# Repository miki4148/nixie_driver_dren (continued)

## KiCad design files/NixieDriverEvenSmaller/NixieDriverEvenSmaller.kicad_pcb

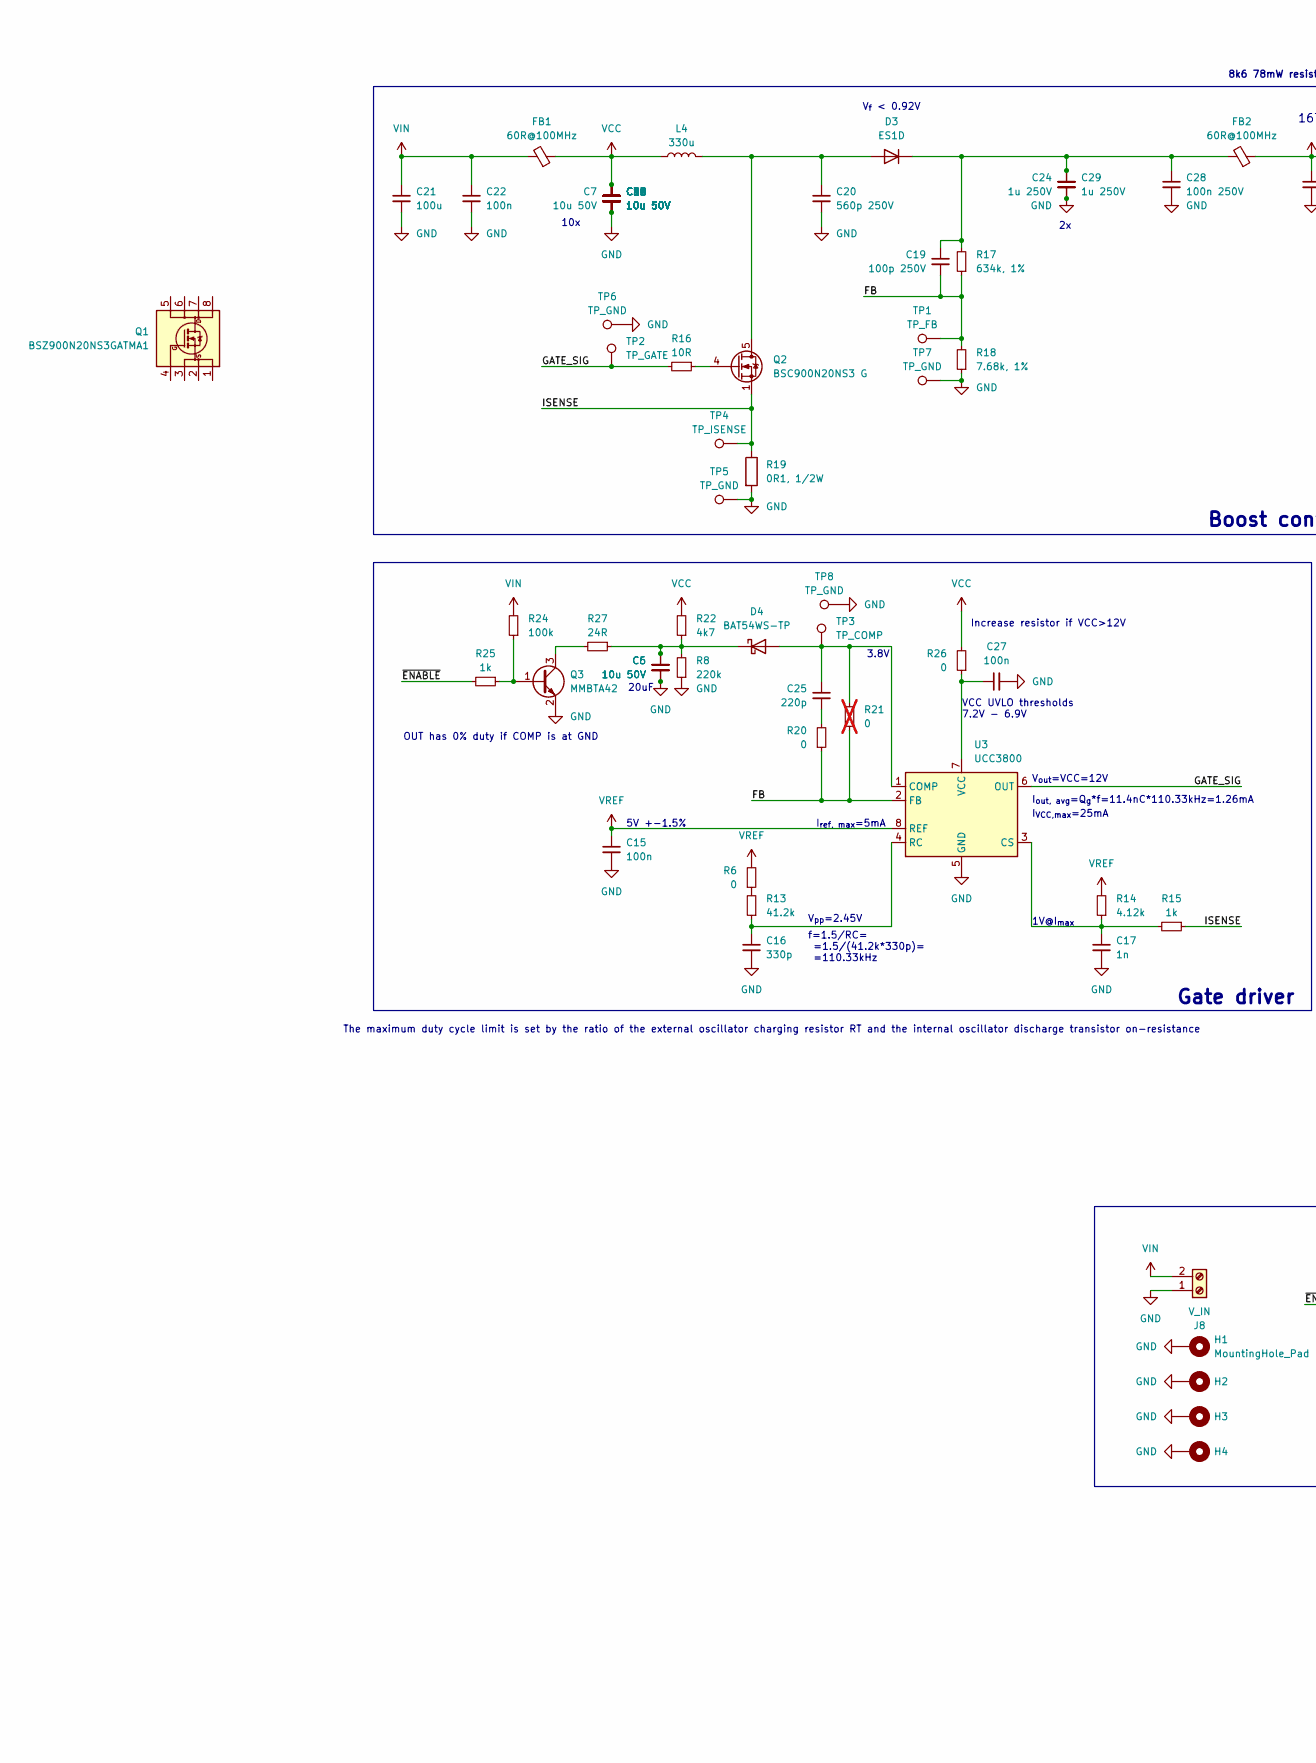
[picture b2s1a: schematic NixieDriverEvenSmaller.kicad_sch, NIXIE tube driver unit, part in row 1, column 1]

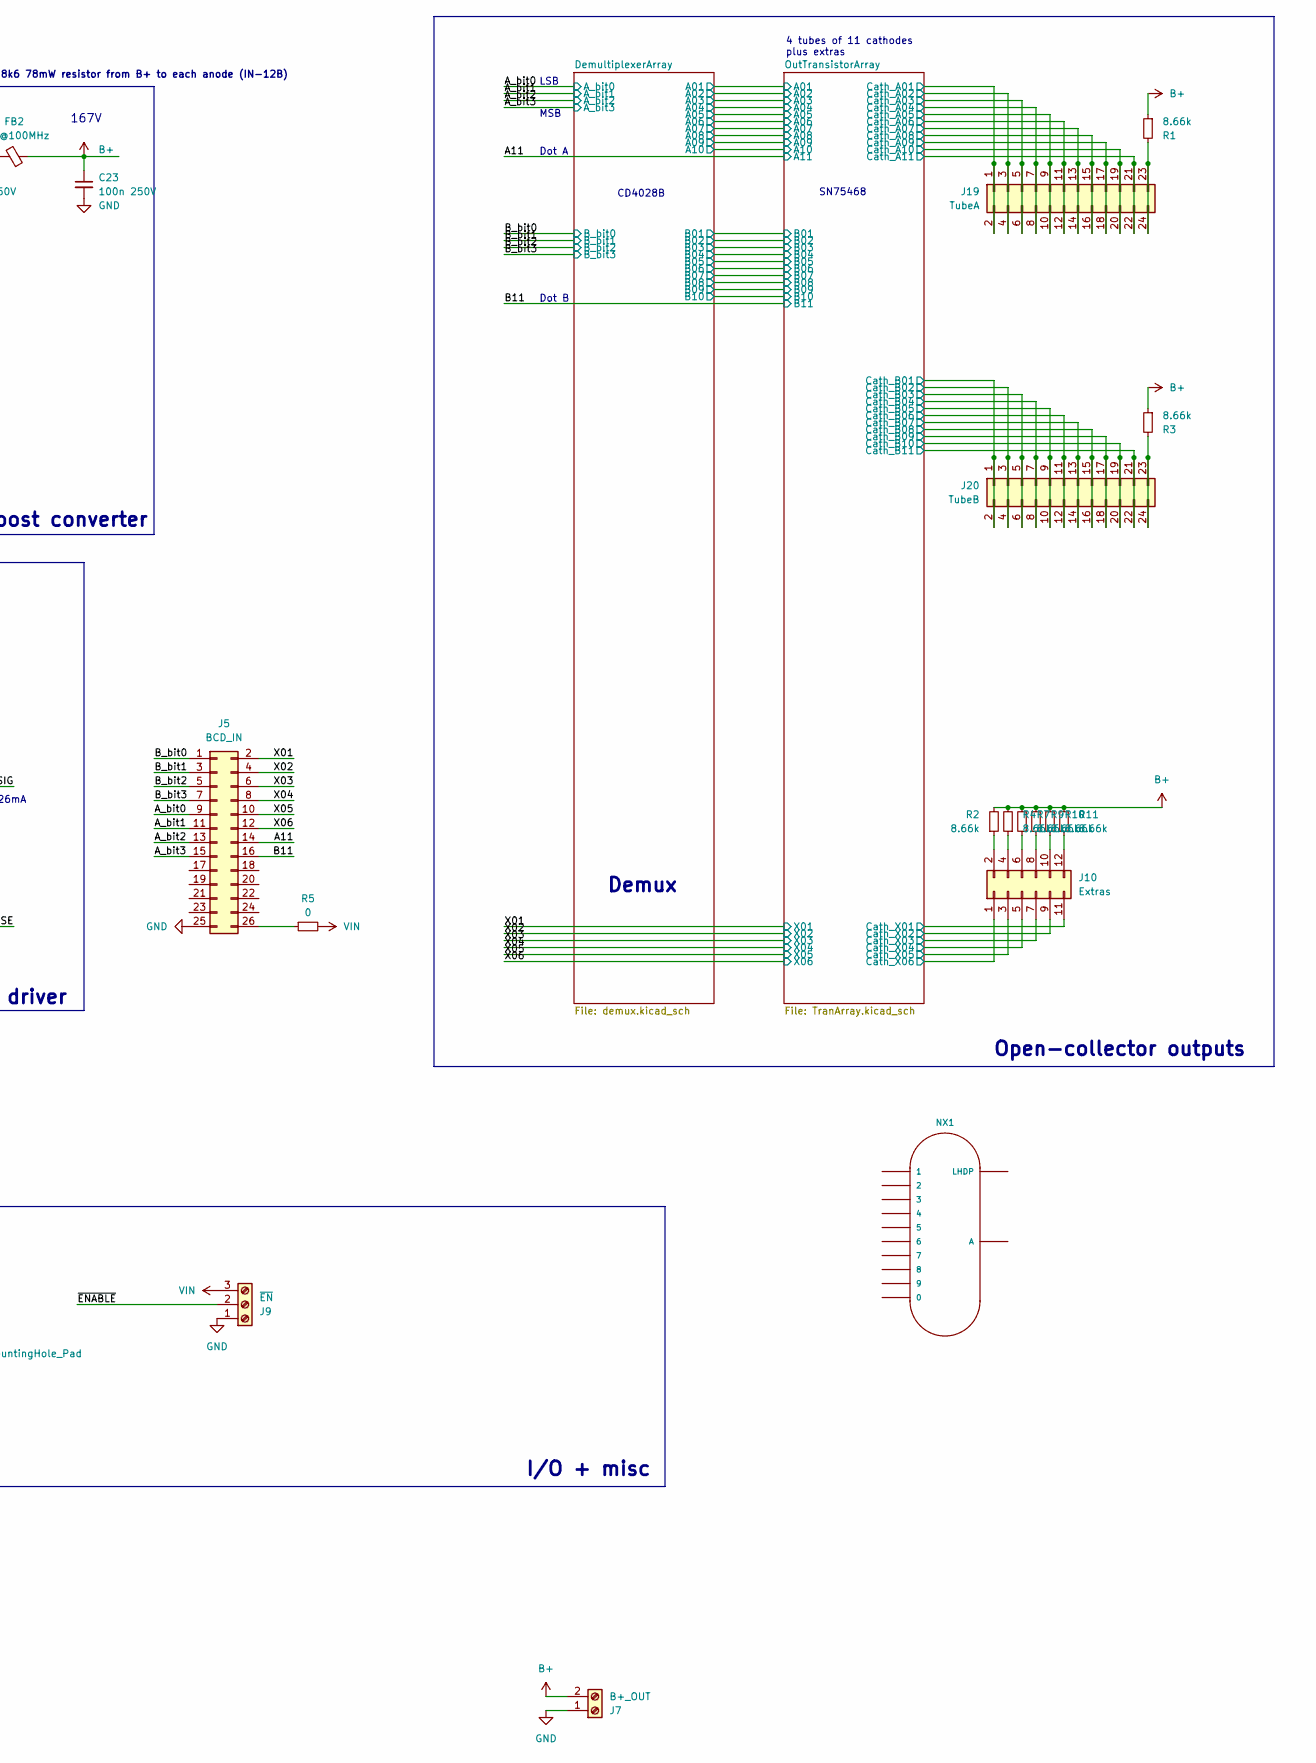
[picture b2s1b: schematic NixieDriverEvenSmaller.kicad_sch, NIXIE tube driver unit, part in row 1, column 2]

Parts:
C5, C6, C7, C8, C9, C10, C11, C12, C13, C14, C18, C30: 10u 50V; C_1206_3216Metric
C15, C22, C27: 100n; C_0603_1608Metric
C16: 330p; C_0603_1608Metric
C17: 1n; C_0603_1608Metric
C19: 100p 250V; C_1206_3216Metric
C20: 560p 250V; C_1206_3216Metric
C21: 100u; C_0603_1608Metric
C23, C28: 100n 250V; C_1206_3216Metric
C24, C29: 1u 250V; C_2220_5750Metric
C25: 220p; C_0603_1608Metric
D3: ES1D; D_SMA
D4: BAT54WS-TP; D_SOD-323_HandSoldering; MPN BAT54WS-7-F
FB1, FB2: 60R@100MHz; L_0603_1608Metric
H1, H2, H3, H4: MountingHole_Pad; MountingHole_3.2mm_M3_Pad
J5: BCD_IN; PinHeader_2x13_P1.27mm_Vertical_SMD
J7: B+_OUT; PinHeader_1x02_P2.00mm_Vertical
J8: V_IN; PinHeader_1x02_P2.00mm_Vertical
J9: ~{EN}; PinHeader_1x03_P2.00mm_Vertical
J10: Extras; PinSocket_2x06_P2.54mm_Vertical
J19: TubeA; PinSocket_2x12_P2.54mm_Vertical
J20: TubeB; PinSocket_2x12_P2.54mm_Vertical
L4: 330u; L_12x12mm_H8mm
NX1: IN-12BORIGINAL; nixies-us_IN-12
Q1: BSZ900N20NS3GATMA1; MPN FDS2672CT-ND
Q2: BSC900N20NS3 G; Infineon_PG-TDSON-8_6.15x5.15mm
Q3: MMBTA42; SOT-23
R1, R2, R3, R4, R7, R9, R10, R11: 8.66k; R_0805_2012Metric_Pad1.20x1.40mm_HandSolder
R5, R6, R20, R26: 0; R_0603_1608Metric
R8: 220k; R_0603_1608Metric
R13: 41.2k; R_0603_1608Metric
R14: 4.12k; R_0603_1608Metric
R15, R25: 1k; R_0603_1608Metric
R16: 10R; R_0603_1608Metric
R17: 634k, 1%; R_1206_3216Metric
R18: 7.68k, 1%; R_1206_3216Metric
R19: 0R1, 1/2W; R_1206_3216Metric
R21: 0; R_0603_1608Metric; not fitted
R22: 4k7; R_0603_1608Metric
R24: 100k; R_0603_1608Metric
R27: 24R; R_0603_1608Metric
TP1: TP_FB; TestPoint_Pad_D1.0mm
TP2: TP_GATE; TestPoint_Pad_D1.0mm
TP3: TP_COMP; TestPoint_Pad_D1.0mm
TP4: TP_ISENSE; TestPoint_Pad_D1.0mm
TP5, TP6, TP7, TP8: TP_GND; TestPoint_Pad_1.0x1.0mm
U3: UCC3800; SOIC-8_3.9x4.9mm_P1.27mm

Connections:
/A11: J5.14; also elsewhere on the board
/A_bit0: J5.9; also elsewhere on the board
/A_bit1: J5.11; also elsewhere on the board
/A_bit2: J5.13; also elsewhere on the board
/A_bit3: J5.15; also elsewhere on the board
/B11: J5.16; also elsewhere on the board
/B_bit0: J5.1; also elsewhere on the board
/B_bit1: J5.3; also elsewhere on the board
/B_bit2: J5.5; also elsewhere on the board
/B_bit3: J5.7; also elsewhere on the board
/FB: C19.2, R17.1, R18.2, R20.1, R21.1, TP1.1, U3.2 (FB)
/GATE_SIG: R16.2, TP2.1, U3.6 (OUT)
/ISENSE: Q2.1 (S), Q2.2 (S), Q2.3 (S), R15.1, R19.1, TP4.1
/OutTransistorArray/Cath_A01: J19.1, J19.2; also elsewhere on the board
/OutTransistorArray/Cath_A02: J19.3, J19.4; also elsewhere on the board
/OutTransistorArray/Cath_A03: J19.5, J19.6; also elsewhere on the board
/OutTransistorArray/Cath_A04: J19.7, J19.8; also elsewhere on the board
/OutTransistorArray/Cath_A05: J19.9, J19.10; also elsewhere on the board
/OutTransistorArray/Cath_A06: J19.11, J19.12; also elsewhere on the board
/OutTransistorArray/Cath_A07: J19.13, J19.14; also elsewhere on the board
/OutTransistorArray/Cath_A08: J19.15, J19.16; also elsewhere on the board
/OutTransistorArray/Cath_A09: J19.17, J19.18; also elsewhere on the board
/OutTransistorArray/Cath_A10: J19.19, J19.20; also elsewhere on the board
/OutTransistorArray/Cath_A11: J19.21, J19.22; also elsewhere on the board
/OutTransistorArray/Cath_B01: J20.1, J20.2; also elsewhere on the board
/OutTransistorArray/Cath_B02: J20.3, J20.4; also elsewhere on the board
/OutTransistorArray/Cath_B03: J20.5, J20.6; also elsewhere on the board
/OutTransistorArray/Cath_B04: J20.7, J20.8; also elsewhere on the board
/OutTransistorArray/Cath_B05: J20.9, J20.10; also elsewhere on the board
/OutTransistorArray/Cath_B06: J20.11, J20.12; also elsewhere on the board
/OutTransistorArray/Cath_B07: J20.13, J20.14; also elsewhere on the board
/OutTransistorArray/Cath_B08: J20.15, J20.16; also elsewhere on the board
/OutTransistorArray/Cath_B09: J20.17, J20.18; also elsewhere on the board
/OutTransistorArray/Cath_B10: J20.19, J20.20; also elsewhere on the board
/OutTransistorArray/Cath_B11: J20.21, J20.22; also elsewhere on the board
/OutTransistorArray/Cath_X01: J10.11; also elsewhere on the board
/OutTransistorArray/Cath_X02: J10.9; also elsewhere on the board
/OutTransistorArray/Cath_X03: J10.7; also elsewhere on the board
/OutTransistorArray/Cath_X04: J10.5; also elsewhere on the board
/OutTransistorArray/Cath_X05: J10.3; also elsewhere on the board
/OutTransistorArray/Cath_X06: J10.1; also elsewhere on the board
/X01: J5.2; also elsewhere on the board
/X02: J5.4; also elsewhere on the board
/X03: J5.6; also elsewhere on the board
/X04: J5.8; also elsewhere on the board
/X05: J5.10; also elsewhere on the board
/X06: J5.12; also elsewhere on the board
/~ENABLE: J9.2, R25.2
B+: C23.1, FB2.1, J7.2, R1.1, R2.2, R3.1, R4.2, R7.2, R9.2, R10.2, R11.2
GND: C5.2, C6.2, C7.2, C8.2, C9.2, C10.2, C11.2, C12.2, C13.2, C14.2, C15.2, C16.2, C17.2, C18.2, C20.2, C21.2, C22.2, C23.2, C24.2, C27.2, C28.2, C29.2, C30.2, H1.1, H2.1, H3.1, H4.1, J5.25, J7.1, J8.1, J9.1, Q3.2 (E), R8.1, R18.1, R19.2, TP5.1, TP6.1, TP7.1, TP8.1, U3.5 (GND); also elsewhere on the board
unnamed: C25.2, R20.2
unnamed: C20.1, D3.2 (A), L4.2, Q2.5 (D)
unnamed: C19.1, C24.1, C28.1, C29.1, D3.1 (K), FB2.2, R17.2
unnamed: C25.1, D4.2 (A), R21.2, TP3.1, U3.1 (COMP)
unnamed: C5.1, C6.1, D4.1 (K), R8.2, R22.1, R27.1
unnamed: J5.26, R5.1
unnamed: J10.2, R2.1
unnamed: J10.4, R4.1
unnamed: J10.6, R7.1
unnamed: J10.8, R9.1
unnamed: J10.10, R10.1
unnamed: J10.12, R11.1
unnamed: J19.23, J19.24, R1.2
unnamed: J20.23, J20.24, R3.2
unnamed: Q2.4 (G), R16.1
unnamed: Q3.1 (B), R24.1, R25.1
unnamed: Q3.3 (C), R27.2
unnamed: R6.1, R13.2
unnamed: C17.1, R14.1, R15.2, U3.3 (CS)
unnamed: C16.1, R13.1, U3.4 (RC)
unnamed: C27.1, R26.1, U3.7 (VCC)
VCC: C7.1, C8.1, C9.1, C10.1, C11.1, C12.1, C13.1, C14.1, C18.1, C30.1, FB1.1, L4.1, R22.2, R26.2
VIN: C21.1, C22.1, FB1.2, J8.2, J9.3, R5.2, R24.2; also elsewhere on the board
VREF: C15.1, R6.2, R14.2, U3.8 (REF)

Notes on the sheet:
4 tubes of 11 cathodes plus extras
8k6 78mW resistor from B+ to each anode (IN-12B)
Dot A
I_{ref, max}=5mA
OUT has 0% duty if COMP is at GND
I_{VCC,max}=25mA
1V@I_{max}
10x
V_{out}=VCC=12V
MSB
20uF
167V
f=1.5/RC= =1.5/(41.2k*330p)= =110.33kHz
3.8V
I/O + misc
Demux
CD4028B
V_{f} < 0.92V
Gate driver
I_{out, avg}=Q_{g}*f=11.4nC*110.33kHz=1.26mA
VCC UVLO thresholds 7.2V - 6.9V
V_{pp}=2.45V
The maximum duty cycle limit is set by the ratio of the external oscillator charging resistor RT and the internal oscillator discharge transistor on-resistance
Increase resistor if VCC>12V
SN75468
5V +-1.5%
Boost converter
Dot B
LSB
Open-collector outputs

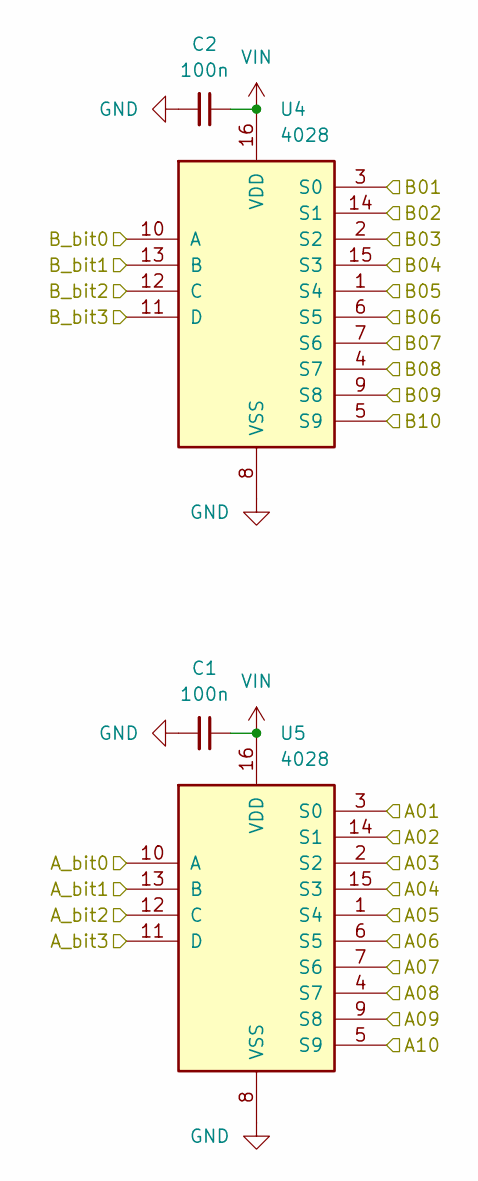
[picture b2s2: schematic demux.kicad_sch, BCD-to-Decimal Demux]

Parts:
C1, C2: 100n; C_0603_1608Metric
U4, U5: 4028; SOIC-16_3.9x9.9mm_P1.27mm

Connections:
/A_bit0: U5.10 (A); also elsewhere on the board
/A_bit1: U5.13 (B); also elsewhere on the board
/A_bit2: U5.12 (C); also elsewhere on the board
/A_bit3: U5.11 (D); also elsewhere on the board
/B_bit0: U4.10 (A); also elsewhere on the board
/B_bit1: U4.13 (B); also elsewhere on the board
/B_bit2: U4.12 (C); also elsewhere on the board
/B_bit3: U4.11 (D); also elsewhere on the board
/DemultiplexerArray/A01: U5.3 (S0); also elsewhere on the board
/DemultiplexerArray/A02: U5.14 (S1); also elsewhere on the board
/DemultiplexerArray/A03: U5.2 (S2); also elsewhere on the board
/DemultiplexerArray/A04: U5.15 (S3); also elsewhere on the board
/DemultiplexerArray/A05: U5.1 (S4); also elsewhere on the board
/DemultiplexerArray/A06: U5.6 (S5); also elsewhere on the board
/DemultiplexerArray/A07: U5.7 (S6); also elsewhere on the board
/DemultiplexerArray/A08: U5.4 (S7); also elsewhere on the board
/DemultiplexerArray/A09: U5.9 (S8); also elsewhere on the board
/DemultiplexerArray/A10: U5.5 (S9); also elsewhere on the board
/DemultiplexerArray/B01: U4.3 (S0); also elsewhere on the board
/DemultiplexerArray/B02: U4.14 (S1); also elsewhere on the board
/DemultiplexerArray/B03: U4.2 (S2); also elsewhere on the board
/DemultiplexerArray/B04: U4.15 (S3); also elsewhere on the board
/DemultiplexerArray/B05: U4.1 (S4); also elsewhere on the board
/DemultiplexerArray/B06: U4.6 (S5); also elsewhere on the board
/DemultiplexerArray/B07: U4.7 (S6); also elsewhere on the board
/DemultiplexerArray/B08: U4.4 (S7); also elsewhere on the board
/DemultiplexerArray/B09: U4.9 (S8); also elsewhere on the board
/DemultiplexerArray/B10: U4.5 (S9); also elsewhere on the board
GND: C1.2, C2.2, U4.8 (VSS), U5.8 (VSS); also elsewhere on the board
VIN: C1.1, C2.1, U4.16 (VDD), U5.16 (VDD); also elsewhere on the board

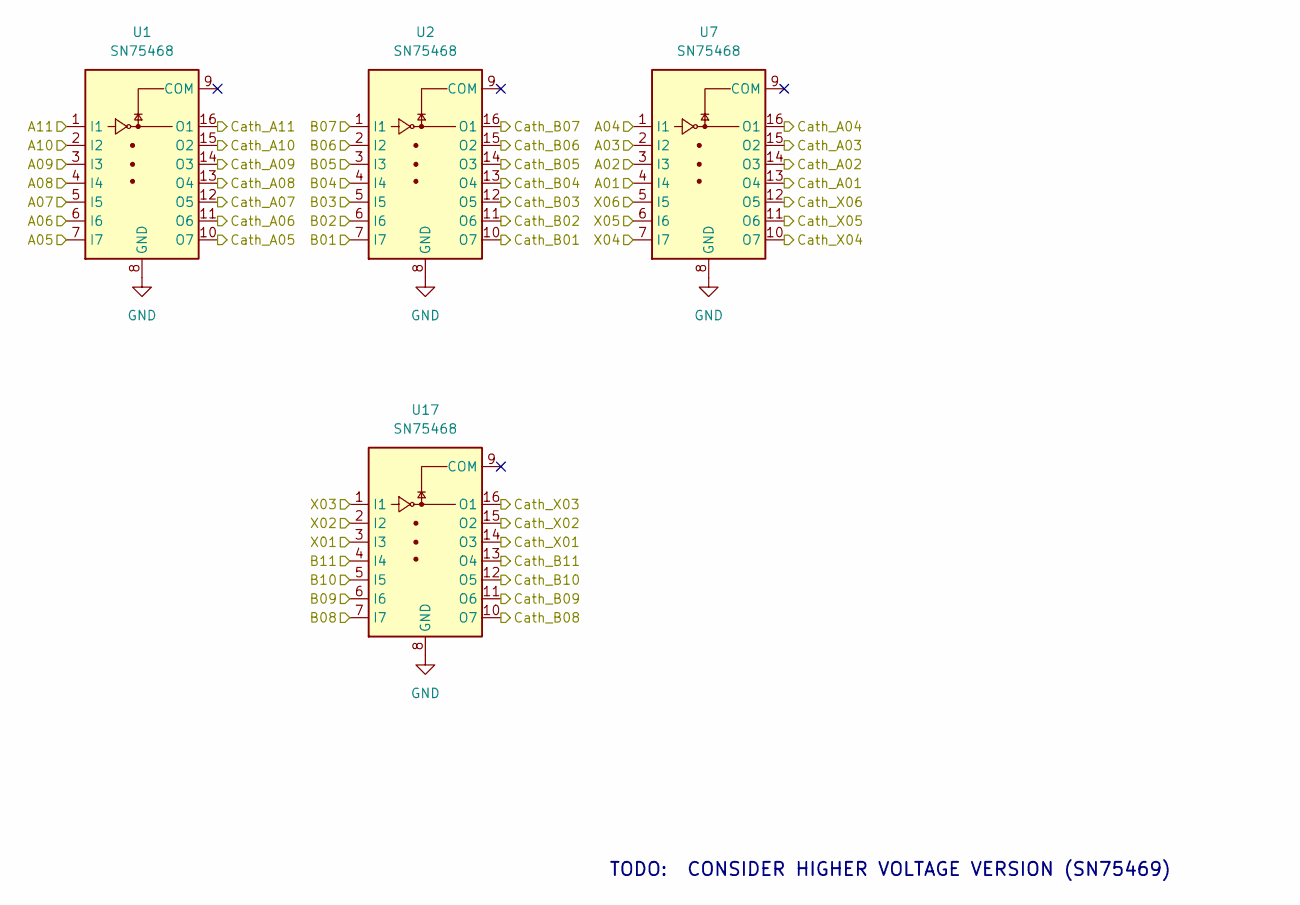
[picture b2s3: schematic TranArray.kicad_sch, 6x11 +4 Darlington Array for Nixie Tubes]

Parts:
U1, U2, U7, U17: SN75468; SOIC-16_3.9x9.9mm_P1.27mm

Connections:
/A11: U1.1 (I1); also elsewhere on the board
/B11: U17.4 (I4); also elsewhere on the board
/DemultiplexerArray/A01: U7.4 (I4); also elsewhere on the board
/DemultiplexerArray/A02: U7.3 (I3); also elsewhere on the board
/DemultiplexerArray/A03: U7.2 (I2); also elsewhere on the board
/DemultiplexerArray/A04: U7.1 (I1); also elsewhere on the board
/DemultiplexerArray/A05: U1.7 (I7); also elsewhere on the board
/DemultiplexerArray/A06: U1.6 (I6); also elsewhere on the board
/DemultiplexerArray/A07: U1.5 (I5); also elsewhere on the board
/DemultiplexerArray/A08: U1.4 (I4); also elsewhere on the board
/DemultiplexerArray/A09: U1.3 (I3); also elsewhere on the board
/DemultiplexerArray/A10: U1.2 (I2); also elsewhere on the board
/DemultiplexerArray/B01: U2.7 (I7); also elsewhere on the board
/DemultiplexerArray/B02: U2.6 (I6); also elsewhere on the board
/DemultiplexerArray/B03: U2.5 (I5); also elsewhere on the board
/DemultiplexerArray/B04: U2.4 (I4); also elsewhere on the board
/DemultiplexerArray/B05: U2.3 (I3); also elsewhere on the board
/DemultiplexerArray/B06: U2.2 (I2); also elsewhere on the board
/DemultiplexerArray/B07: U2.1 (I1); also elsewhere on the board
/DemultiplexerArray/B08: U17.7 (I7); also elsewhere on the board
/DemultiplexerArray/B09: U17.6 (I6); also elsewhere on the board
/DemultiplexerArray/B10: U17.5 (I5); also elsewhere on the board
/OutTransistorArray/Cath_A01: U7.13 (O4); also elsewhere on the board
/OutTransistorArray/Cath_A02: U7.14 (O3); also elsewhere on the board
/OutTransistorArray/Cath_A03: U7.15 (O2); also elsewhere on the board
/OutTransistorArray/Cath_A04: U7.16 (O1); also elsewhere on the board
/OutTransistorArray/Cath_A05: U1.10 (O7); also elsewhere on the board
/OutTransistorArray/Cath_A06: U1.11 (O6); also elsewhere on the board
/OutTransistorArray/Cath_A07: U1.12 (O5); also elsewhere on the board
/OutTransistorArray/Cath_A08: U1.13 (O4); also elsewhere on the board
/OutTransistorArray/Cath_A09: U1.14 (O3); also elsewhere on the board
/OutTransistorArray/Cath_A10: U1.15 (O2); also elsewhere on the board
/OutTransistorArray/Cath_A11: U1.16 (O1); also elsewhere on the board
/OutTransistorArray/Cath_B01: U2.10 (O7); also elsewhere on the board
/OutTransistorArray/Cath_B02: U2.11 (O6); also elsewhere on the board
/OutTransistorArray/Cath_B03: U2.12 (O5); also elsewhere on the board
/OutTransistorArray/Cath_B04: U2.13 (O4); also elsewhere on the board
/OutTransistorArray/Cath_B05: U2.14 (O3); also elsewhere on the board
/OutTransistorArray/Cath_B06: U2.15 (O2); also elsewhere on the board
/OutTransistorArray/Cath_B07: U2.16 (O1); also elsewhere on the board
/OutTransistorArray/Cath_B08: U17.10 (O7); also elsewhere on the board
/OutTransistorArray/Cath_B09: U17.11 (O6); also elsewhere on the board
/OutTransistorArray/Cath_B10: U17.12 (O5); also elsewhere on the board
/OutTransistorArray/Cath_B11: U17.13 (O4); also elsewhere on the board
/OutTransistorArray/Cath_X01: U17.14 (O3); also elsewhere on the board
/OutTransistorArray/Cath_X02: U17.15 (O2); also elsewhere on the board
/OutTransistorArray/Cath_X03: U17.16 (O1); also elsewhere on the board
/OutTransistorArray/Cath_X04: U7.10 (O7); also elsewhere on the board
/OutTransistorArray/Cath_X05: U7.11 (O6); also elsewhere on the board
/OutTransistorArray/Cath_X06: U7.12 (O5); also elsewhere on the board
/X01: U17.3 (I3); also elsewhere on the board
/X02: U17.2 (I2); also elsewhere on the board
/X03: U17.1 (I1); also elsewhere on the board
/X04: U7.7 (I7); also elsewhere on the board
/X05: U7.6 (I6); also elsewhere on the board
/X06: U7.5 (I5); also elsewhere on the board
GND: U1.8 (GND), U2.8 (GND), U7.8 (GND), U17.8 (GND); also elsewhere on the board

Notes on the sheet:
TODO: CONSIDER HIGHER VOLTAGE VERSION (SN75469)

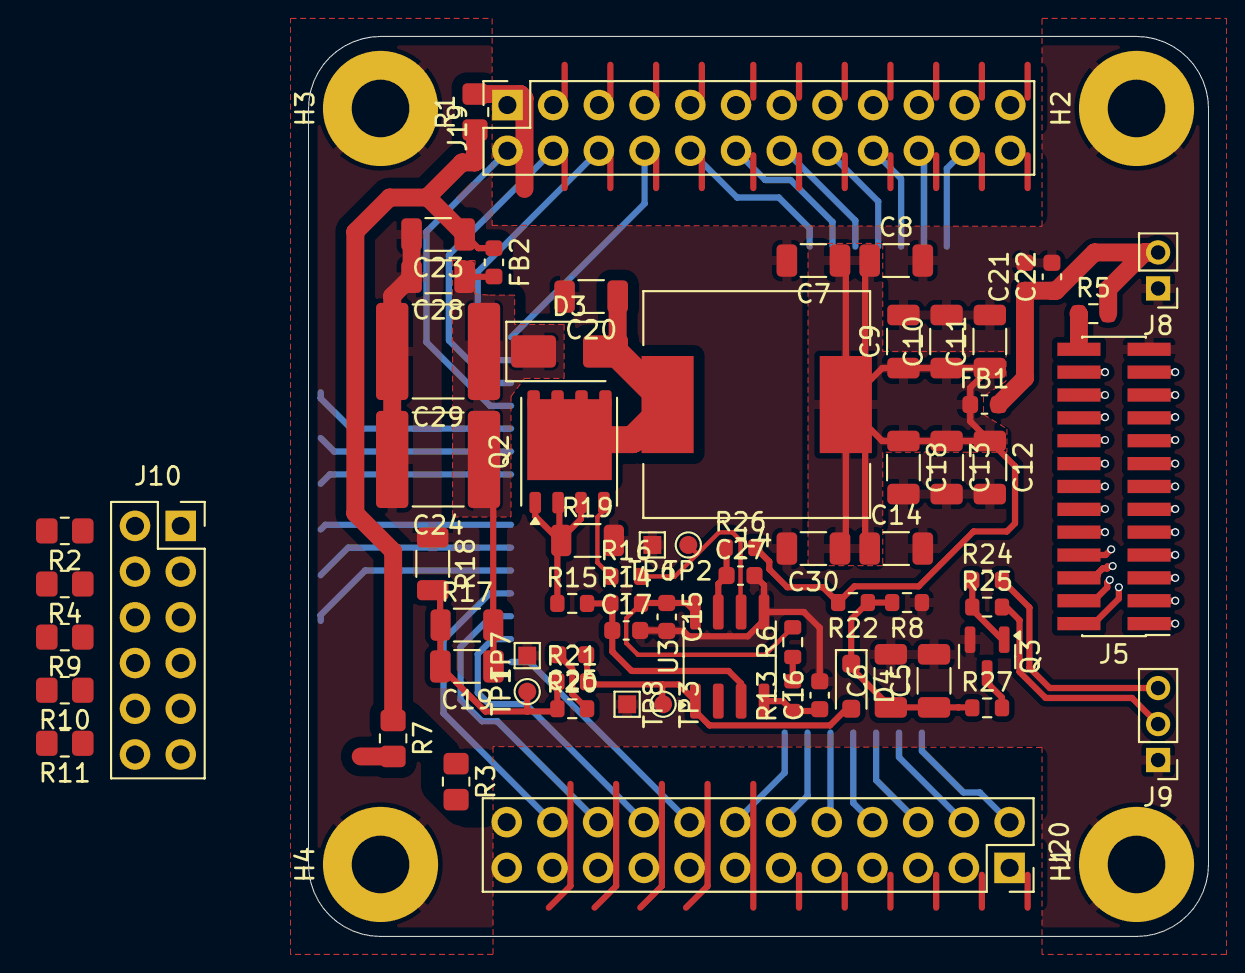
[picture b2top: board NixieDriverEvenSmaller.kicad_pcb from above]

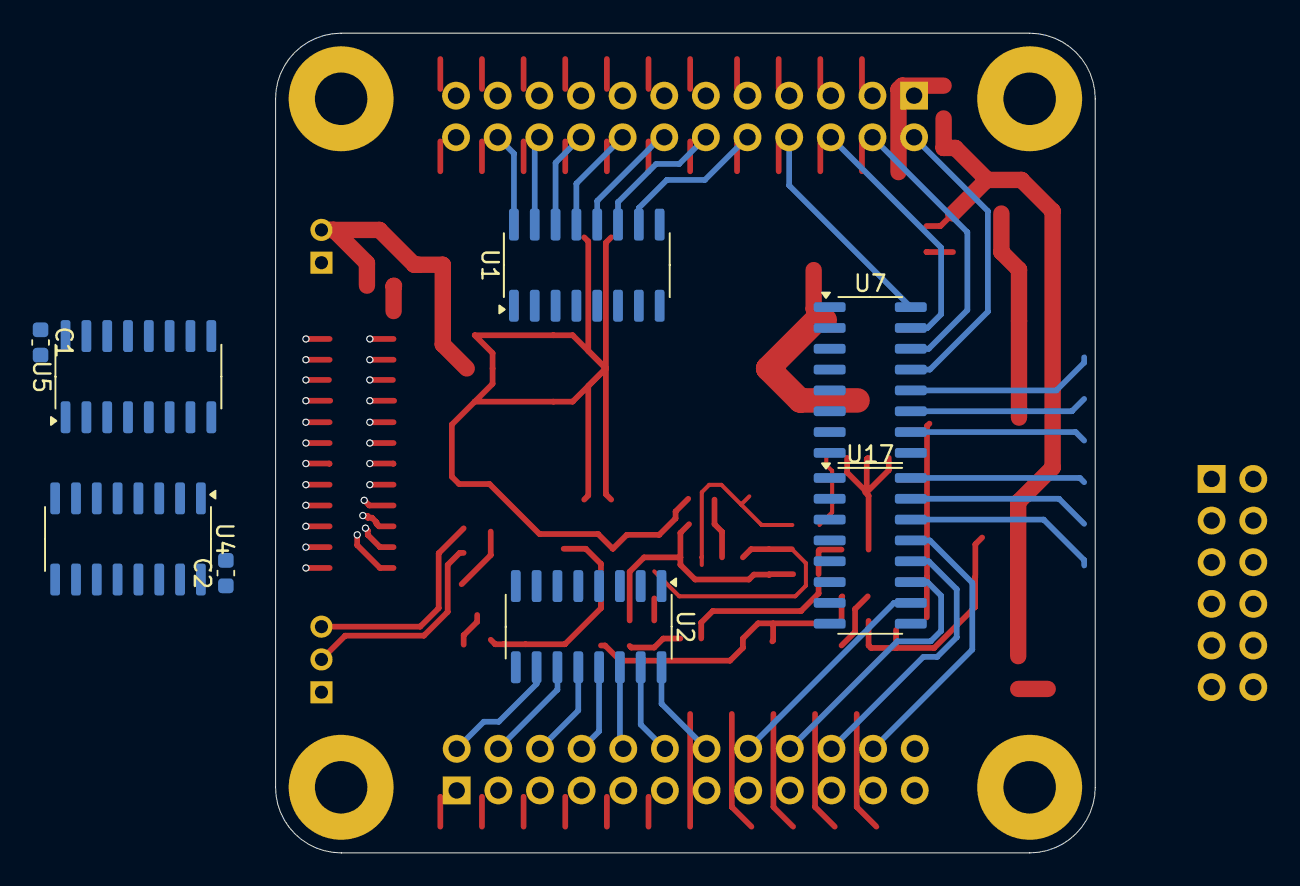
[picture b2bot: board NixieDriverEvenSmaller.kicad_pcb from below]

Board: 8 copper layers, 50.0 x 50.0 mm, 82 parts (8 on the bottom side), 94 nets.

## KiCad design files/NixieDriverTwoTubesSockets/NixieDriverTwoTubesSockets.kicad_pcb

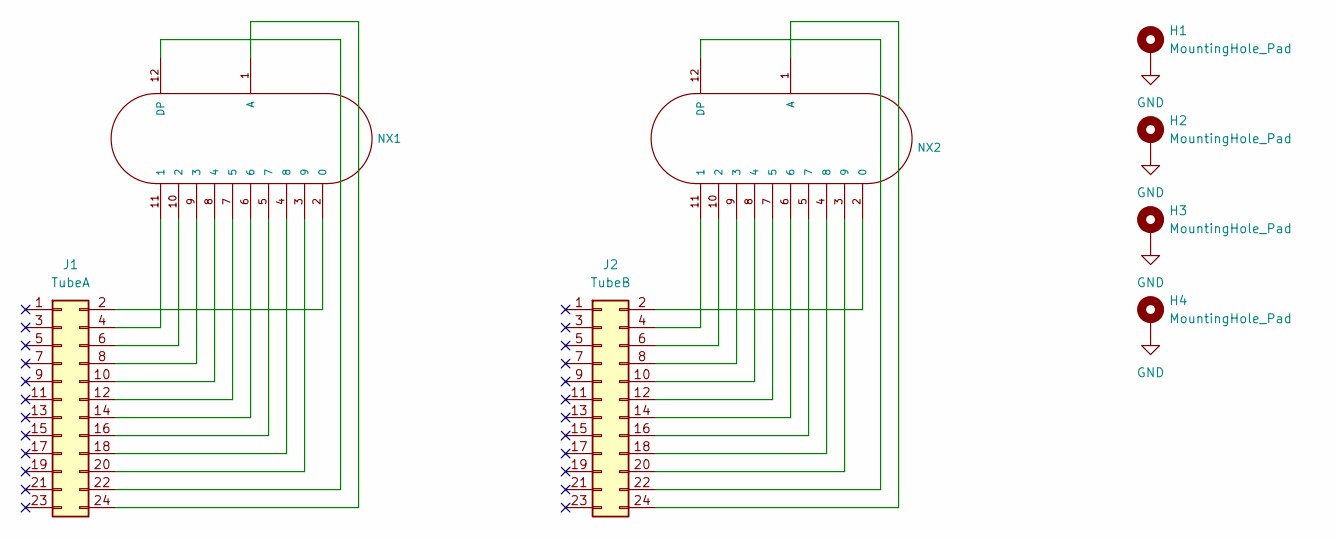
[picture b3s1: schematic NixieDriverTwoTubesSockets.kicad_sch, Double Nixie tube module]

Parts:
H1, H2, H3, H4: MountingHole_Pad; MountingHole_3.2mm_M3_Pad
J1: TubeA; PinHeader_2x12_P2.54mm_Vertical
J2: TubeB; PinHeader_2x12_P2.54mm_Vertical
NX1, NX2: IN-12BIN-12-DSUB; IN_12B_Socket

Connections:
GND: H1.1, H2.1, H3.1, H4.1
unnamed: J1.2, NX1.2 (0)
unnamed: J1.4, NX1.11 (1)
unnamed: J1.6, NX1.10 (2)
unnamed: J1.8, NX1.9 (3)
unnamed: J1.10, NX1.8 (4)
unnamed: J1.12, NX1.7 (5)
unnamed: J1.14, NX1.6
unnamed: J1.16, NX1.5 (7)
unnamed: J1.18, NX1.4 (8)
unnamed: J1.20, NX1.3 (9)
unnamed: J1.22, NX1.12 (DP)
unnamed: J1.24, NX1.1 (A)
unnamed: J2.2, NX2.2 (0)
unnamed: J2.4, NX2.11 (1)
unnamed: J2.6, NX2.10 (2)
unnamed: J2.8, NX2.9 (3)
unnamed: J2.10, NX2.8 (4)
unnamed: J2.12, NX2.7 (5)
unnamed: J2.14, NX2.6
unnamed: J2.16, NX2.5 (7)
unnamed: J2.18, NX2.4 (8)
unnamed: J2.20, NX2.3 (9)
unnamed: J2.22, NX2.12 (DP)
unnamed: J2.24, NX2.1 (A)

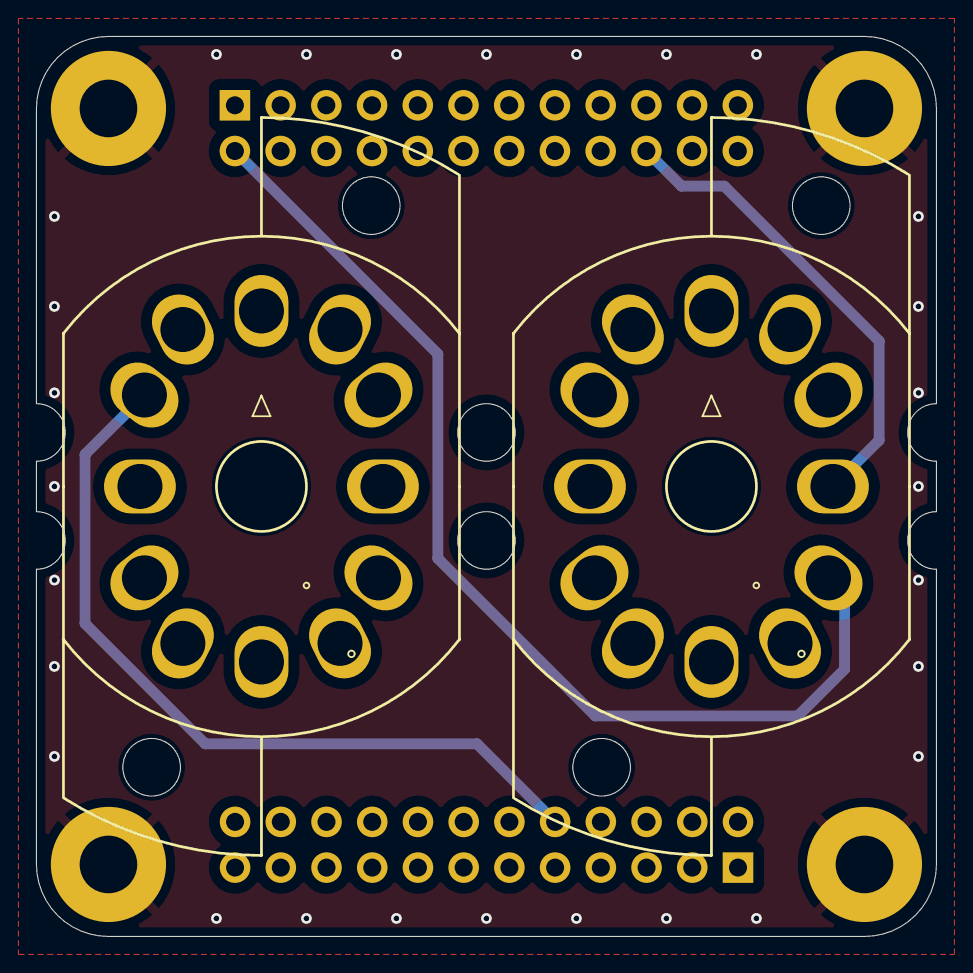
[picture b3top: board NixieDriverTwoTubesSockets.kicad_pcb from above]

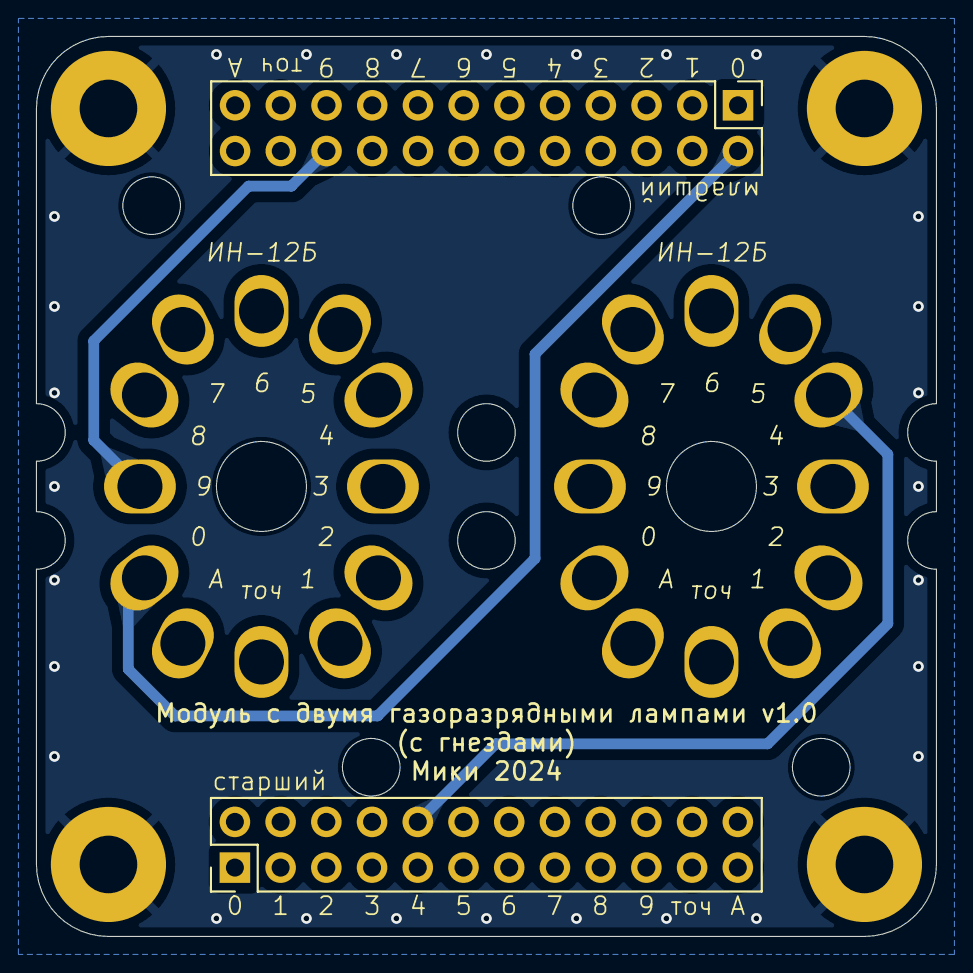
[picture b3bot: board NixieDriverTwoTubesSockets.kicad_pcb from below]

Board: 6 copper layers, 50.0 x 50.0 mm, 8 parts (2 on the bottom side), 25 nets.

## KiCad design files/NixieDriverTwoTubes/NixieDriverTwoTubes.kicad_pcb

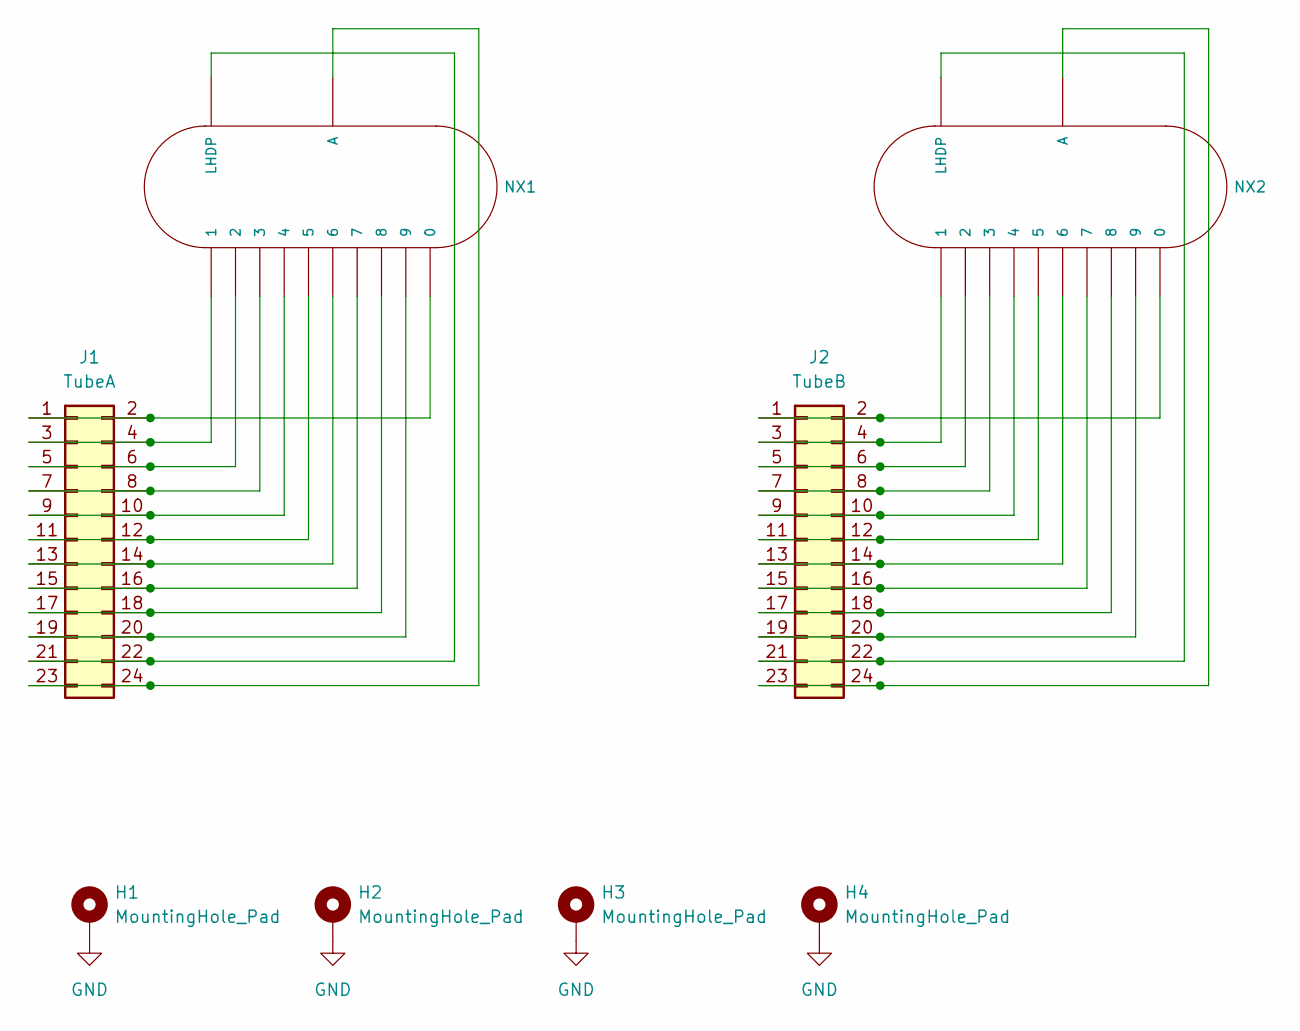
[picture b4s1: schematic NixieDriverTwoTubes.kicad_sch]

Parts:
H1, H2, H3, H4: MountingHole_Pad; MountingHole_3.2mm_M3_Pad
J1: TubeA; PinHeader_2x12_P2.54mm_Vertical
J2: TubeB; PinHeader_2x12_P2.54mm_Vertical
NX1, NX2: IN-12BIN-12-DSUB; nixies-us-IN-12-DSUB

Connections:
GND: H1.1, H2.1, H3.1, H4.1
unnamed: J1.1, J1.2, NX1.0
unnamed: J1.3, J1.4, NX1.1
unnamed: J1.5, J1.6, NX1.2
unnamed: J1.7, J1.8, NX1.3
unnamed: J1.9, J1.10, NX1.4
unnamed: J1.11, J1.12, NX1.5
unnamed: J1.13, J1.14, NX1.6
unnamed: J1.15, J1.16, NX1.7
unnamed: J1.17, J1.18, NX1.8
unnamed: J1.19, J1.20, NX1.9
unnamed: J1.21, J1.22, NX1.LHDP
unnamed: J1.23, J1.24, NX1.A
unnamed: J2.1, J2.2, NX2.0
unnamed: J2.3, J2.4, NX2.1
unnamed: J2.5, J2.6, NX2.2
unnamed: J2.7, J2.8, NX2.3
unnamed: J2.9, J2.10, NX2.4
unnamed: J2.11, J2.12, NX2.5
unnamed: J2.13, J2.14, NX2.6
unnamed: J2.15, J2.16, NX2.7
unnamed: J2.17, J2.18, NX2.8
unnamed: J2.19, J2.20, NX2.9
unnamed: J2.21, J2.22, NX2.LHDP
unnamed: J2.23, J2.24, NX2.A
